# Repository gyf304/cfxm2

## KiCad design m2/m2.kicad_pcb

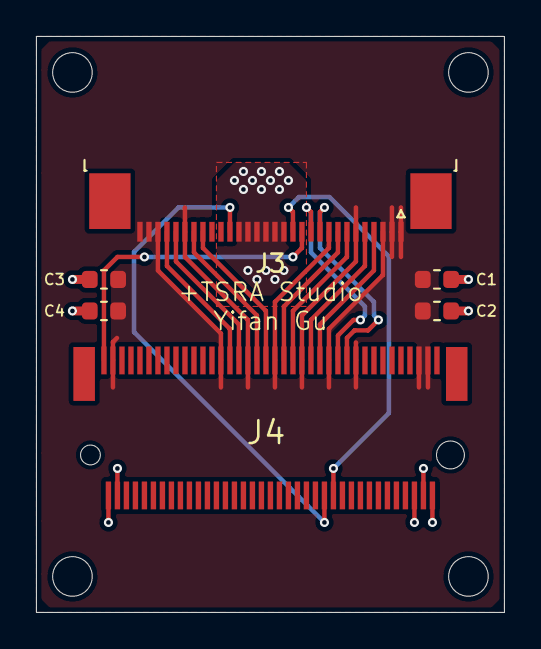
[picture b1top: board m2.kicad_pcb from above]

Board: 2 copper layers, 26.0 x 32.0 mm, 6 parts (0 on the bottom side), 15 nets.

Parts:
C1, C2, C3, C4: C; C_0603_1608Metric
J3: Conn_01x30_Female; TE_3-1734839-0_1x30-1MP_P0.5mm_Horizontal
J4: Conn_M2_Key_M; m2

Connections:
+3.3V: C1.1, C2.1, C3.1, C4.1, J3.14, J3.15, J3.16, J3.17, J3.18, J3.19, J4.2, J4.4, J4.70, J4.72, J4.74
CLKREQ#: J3.13, J4.52
GND: C1.2, C2.2, C3.2, C4.2, J3.1, J3.2, J3.3, J3.6, J3.9, J3.25, J3.28, J3.29, J3.30, J4.3, J4.27, J4.33, J4.39, J4.45, J4.51, J4.57, J4.71, J4.73
INS#: J3.12, J4.1
PERST#: J3.20, J4.50
PERn0: J3.8, J4.41
PERn1: J3.27, J4.29
PERp0: J3.7, J4.43
PERp1: J3.26, J4.31
PETn0: J3.5, J4.47
PETn1: J3.24, J4.35
PETp0: J3.4, J4.49
PETp1: J3.23, J4.37
REFCLK+: J3.10, J4.55
REFCLK-: J3.11, J4.53

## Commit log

2020-08-02 initial
